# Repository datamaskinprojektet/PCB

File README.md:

## Useful links:
[Kicad Library mangement](https://hackaday.com/2017/05/18/kicad-best-practises-library-management/)
[Kicad git integration](https://jnavila.github.io/plotkicadsch/)

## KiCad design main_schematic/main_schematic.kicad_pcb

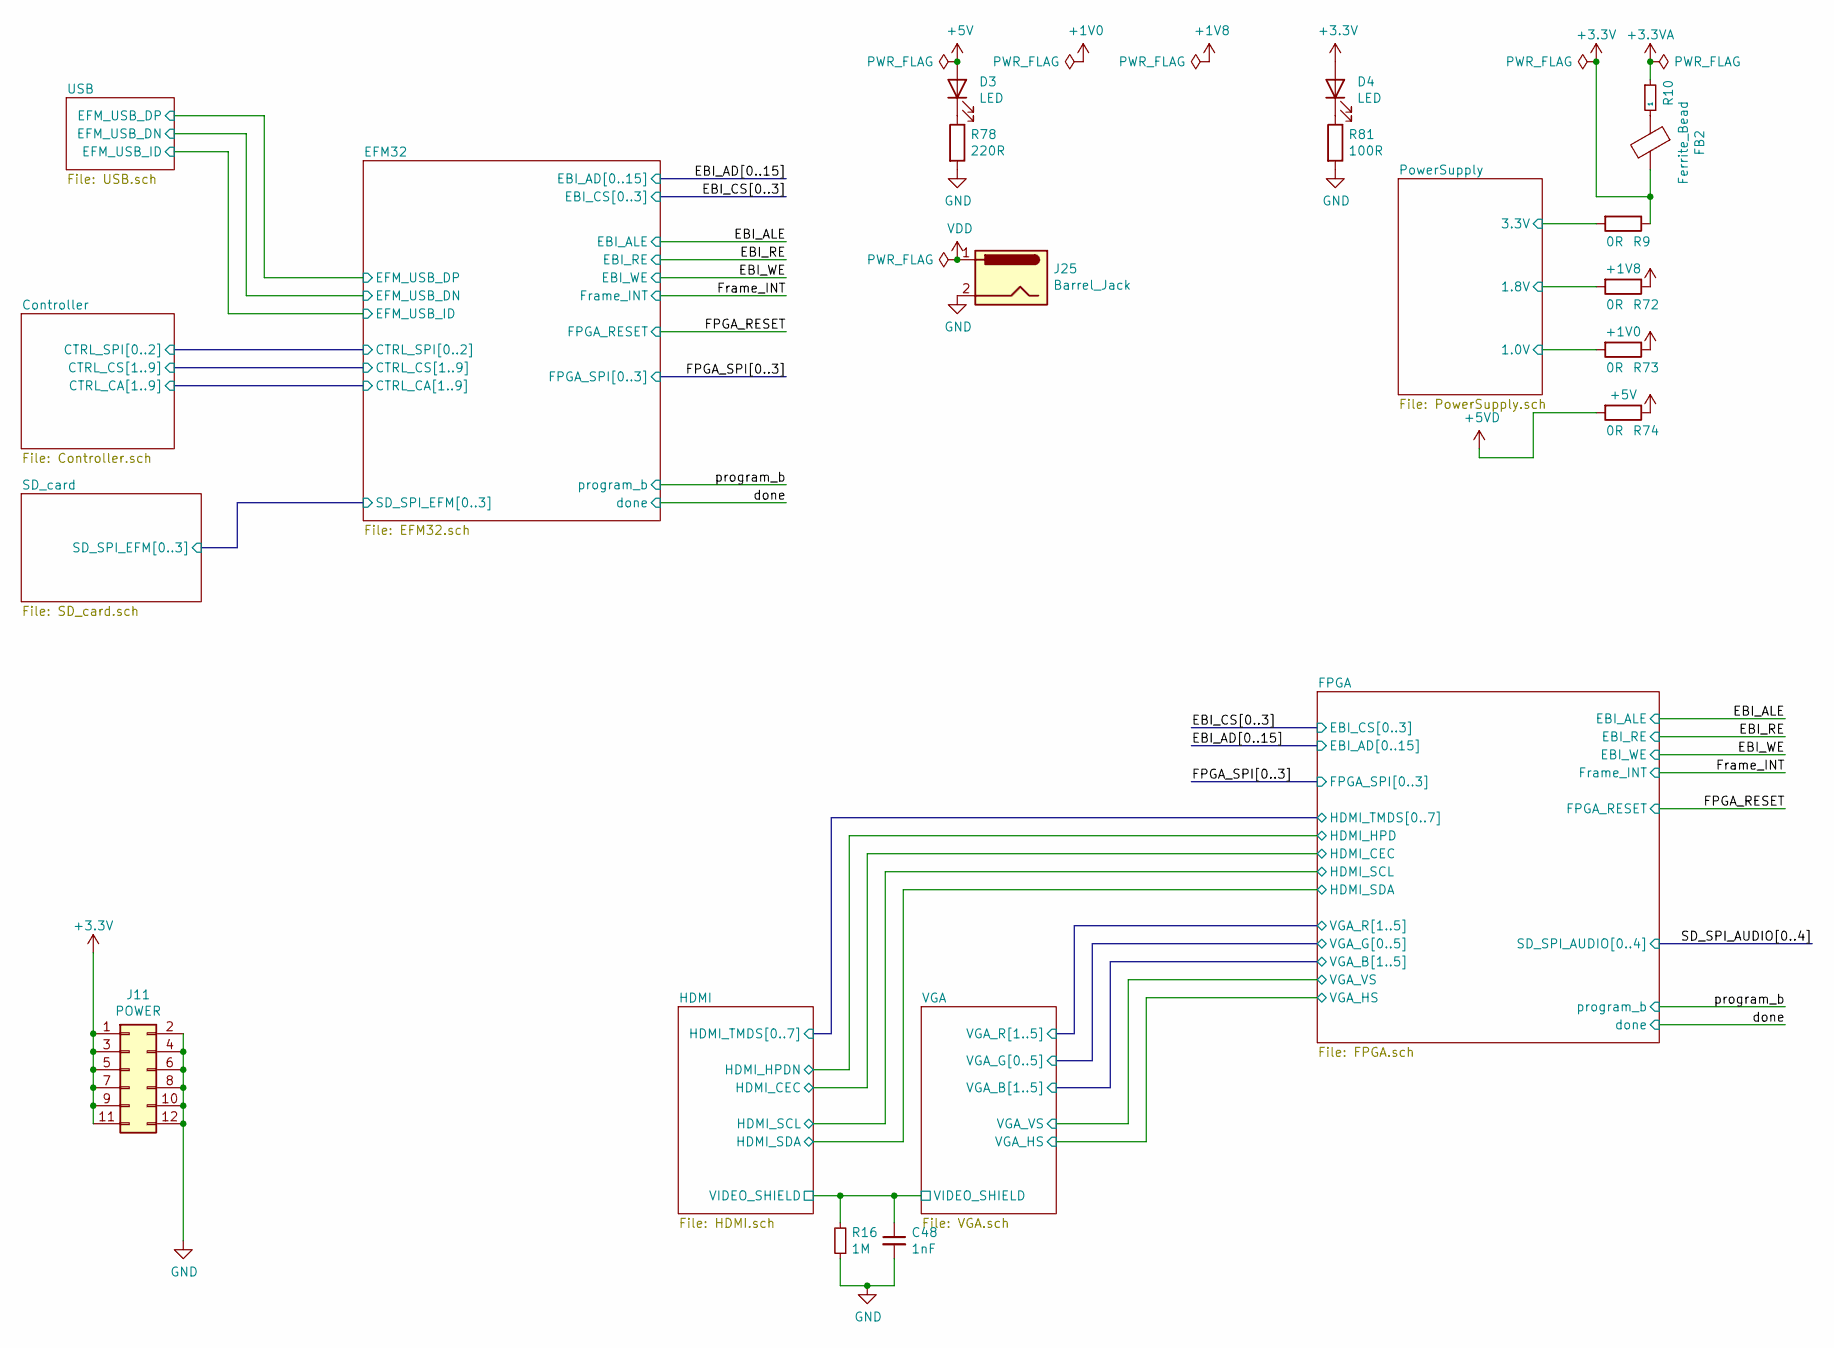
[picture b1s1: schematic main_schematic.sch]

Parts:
C48: 1nF; C_0805_2012Metric
D3, D4: LED; LED_0805_2012Metric
FB2: Ferrite_Bead; R_0805_2012Metric
J11: POWER; PinSocket_2x06_P2.54mm_Vertical_SMD
J25: Barrel_Jack; BarrelJack_Wuerth_6941xx301002
R9, R72, R73, R74: 0R; R_0805_2012Metric
R10: 1; R_0805_2012Metric
R16: 1M; R_0805_2012Metric
R78: 220R; R_0805_2012Metric
R81: 100R; R_0805_2012Metric

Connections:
+1V0: R73.1; also elsewhere on the board
+1V8: R72.1; also elsewhere on the board
+3.3VA: R10.1; also elsewhere on the board
+5V: D3.2 (A), R74.1; also elsewhere on the board
+5VD: R74.2; also elsewhere on the board
/HDMI/VIDEO_SHIELD: C48.1, R16.2; also elsewhere on the board
/PowerSupply/1.0V: R73.2; also elsewhere on the board
/PowerSupply/1.8V: R72.2; also elsewhere on the board
/PowerSupply/3.3V: R9.2; also elsewhere on the board
GND: C48.2, J11.2, J11.4, J11.6, J11.8, J11.10, J11.12, J25.2, R16.1, R78.2, R81.2; also elsewhere on the board
unnamed: D3.1 (K), R78.1
unnamed: D4.1 (K), R81.1
unnamed: FB2.1, R10.2
VDD: J25.1; also elsewhere on the board

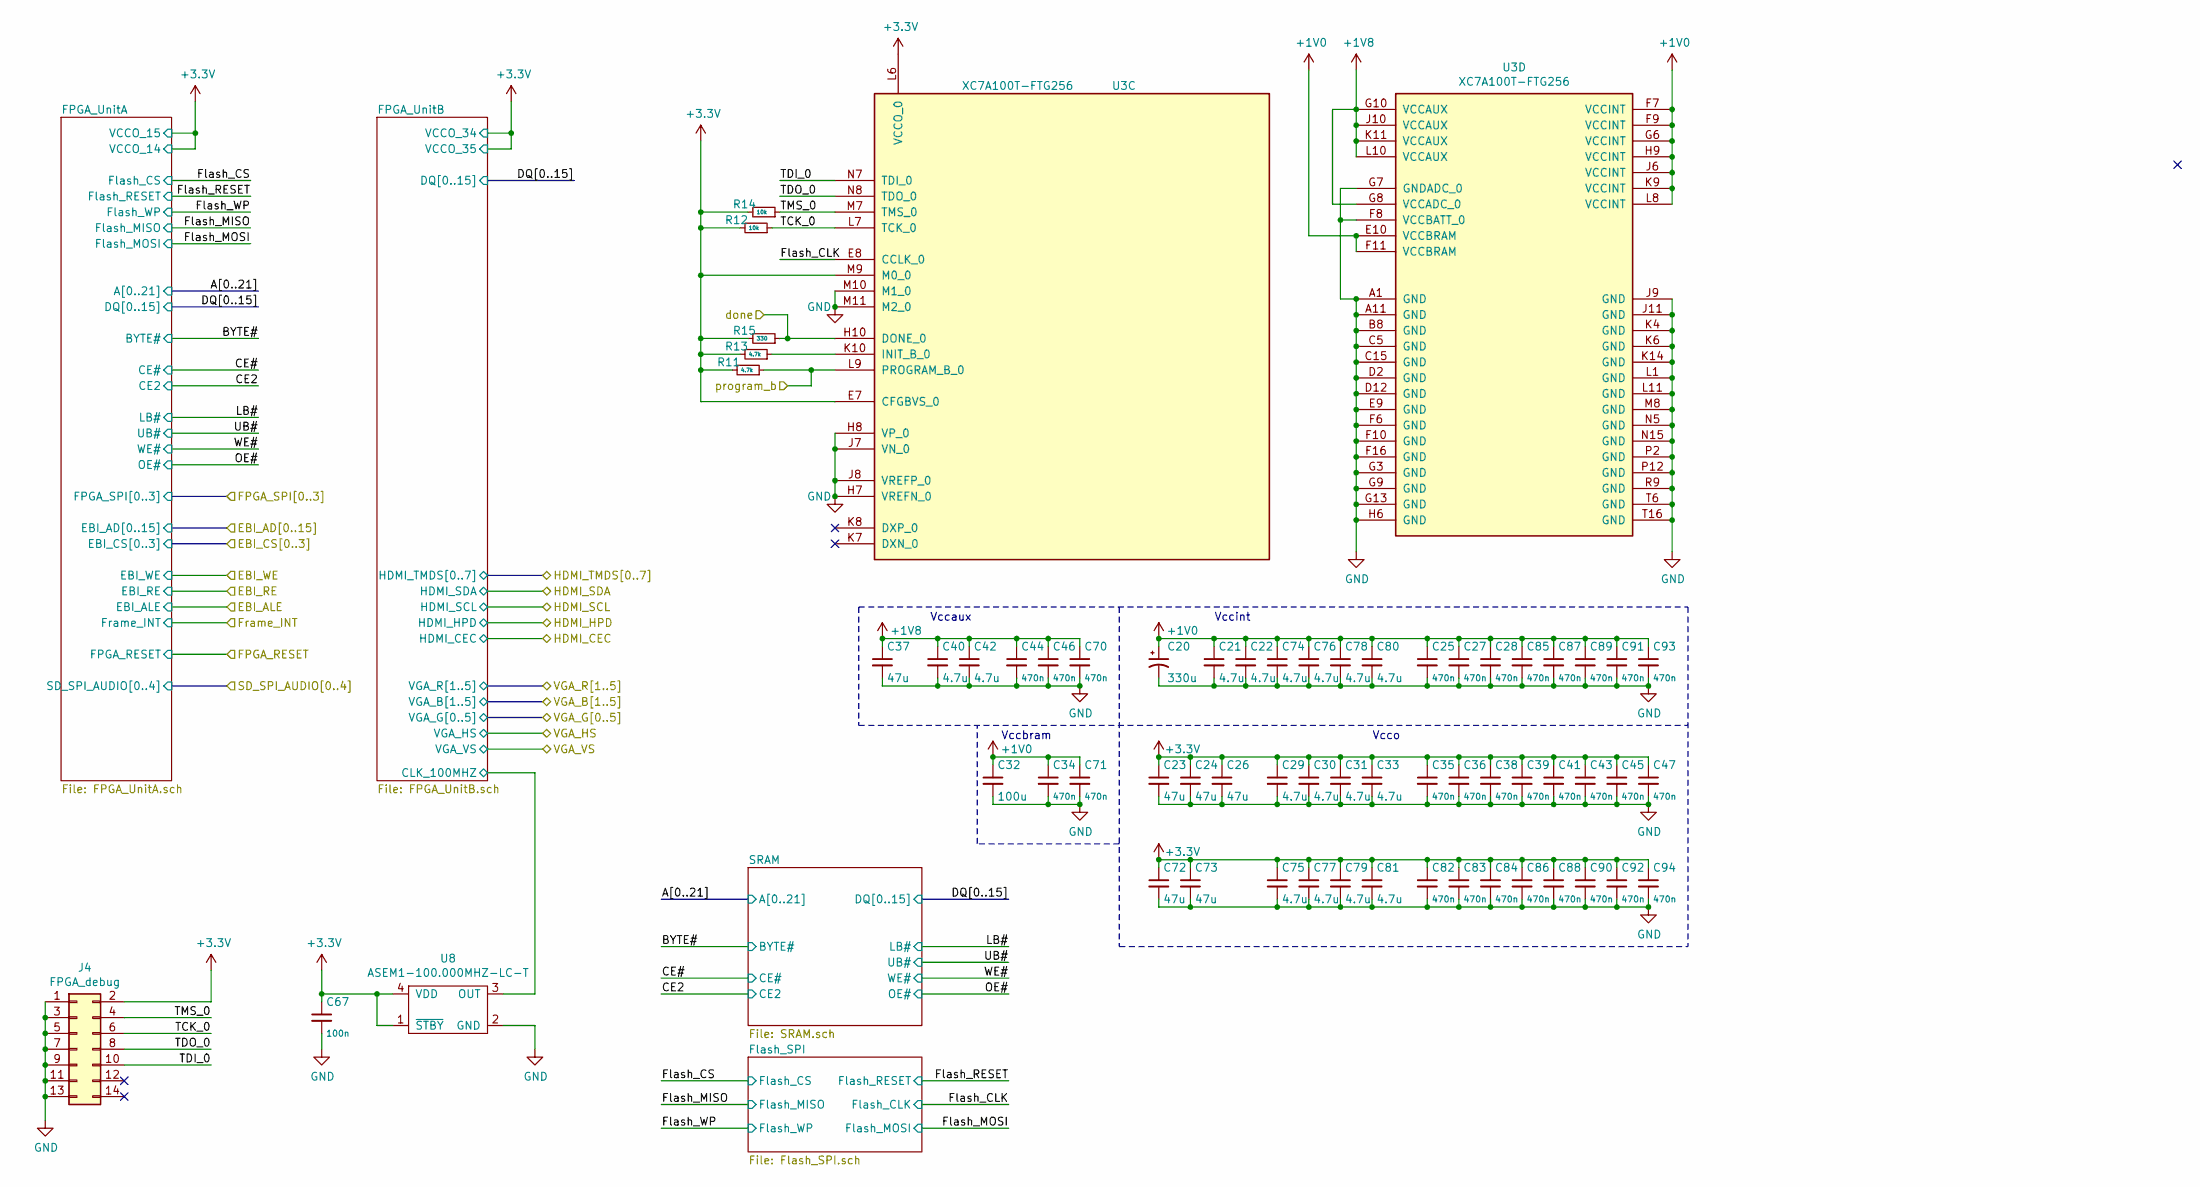
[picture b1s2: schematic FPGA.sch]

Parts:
C20: 330u; CP_EIA-7343-20_Kemet-V
C21, C22, C29, C30, C31, C33, C40, C42, C74, C75, C76, C77, C78, C79, C80, C81: 4.7u; C_0805_2012Metric
C23, C24, C26, C37, C72, C73: 47u; C_1210_3225Metric
C25, C27, C28, C34, C35, C36, C38, C39, C41, C43, C44, C45, C46, C47, C70, C71, C82, C83, C84, C85, C86, C87, C88, C89, C90, C91, C92, C93, C94: 470n; C_0603_1608Metric
C32: 100u; C_1210_3225Metric
C67: 100n; C_0805_2012Metric
J4: FPGA_debug; PinHeader_2x07_P2.00mm_Vertical_SMD
R11, R13: 4.7k; R_0805_2012Metric
R12, R14: 10k; R_0805_2012Metric
R15: 330; R_0805_2012Metric
U3: XC7A100T-FTG256; Xilinx_FTG256
U8: ASEM1-100.000MHZ-LC-T; Oscillator_SMD_Abracon_ASE-4Pin_3.2x2.5mm

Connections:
+1V0: C20.1, C21.1, C22.1, C25.1, C27.1, C28.1, C32.1, C34.1, C71.1, C74.1, C76.1, C78.1, C80.1, C85.1, C87.1, C89.1, C91.1, C93.1, U3.E10 (VCCBRAM), U3.F7 (VCCINT), U3.F9 (VCCINT), U3.F11 (VCCBRAM), U3.G6 (VCCINT), U3.H9 (VCCINT), U3.J6 (VCCINT), U3.K9 (VCCINT), U3.L8 (VCCINT); also elsewhere on the board
+1V8: C37.1, C40.1, C42.1, C44.1, C46.1, C70.1, U3.G8 (VCCADC_0), U3.G10 (VCCAUX), U3.J10 (VCCAUX), U3.K11 (VCCAUX), U3.L10 (VCCAUX); also elsewhere on the board
/FPGA/FPGA_UnitB/CLK_100MHZ: U8.3 (OUT); also elsewhere on the board
/FPGA/Flash_CLK: U3.E8 (CCLK_0); also elsewhere on the board
/FPGA/TCK_0: J4.6, R12.1, U3.L7 (TCK_0)
/FPGA/TDI_0: J4.10, U3.N7 (TDI_0)
/FPGA/TDO_0: J4.8, U3.N8 (TDO_0)
/FPGA/TMS_0: J4.4, R14.1, U3.M7 (TMS_0)
/done: R15.1, U3.H10 (DONE_0); also elsewhere on the board
/program_b: R11.1, U3.L9 (PROGRAM_B_0); also elsewhere on the board
GND: C20.2, C21.2, C22.2, C23.2, C24.2, C25.2, C26.2, C27.2, C28.2, C29.2, C30.2, C31.2, C32.2, C33.2, C34.2, C35.2, C36.2, C37.2, C38.2, C39.2, C40.2, C41.2, C42.2, C43.2, C44.2, C45.2, C46.2, C47.2, C67.2, C70.2, C71.2, C72.2, C73.2, C74.2, C75.2, C76.2, C77.2, C78.2, C79.2, C80.2, C81.2, C82.2, C83.2, C84.2, C85.2, C86.2, C87.2, C88.2, C89.2, C90.2, C91.2, C92.2, C93.2, C94.2, J4.1, J4.3, J4.5, J4.7, J4.9, J4.11, J4.13, U3.A1 (GND), U3.A11 (GND), U3.B8 (GND), U3.C5 (GND), U3.C15 (GND), U3.D2 (GND), U3.D12 (GND), U3.E9 (GND), U3.F6 (GND), U3.F8 (VCCBATT_0), U3.F10 (GND), U3.F16 (GND), U3.G3 (GND), U3.G7 (GNDADC_0), U3.G9 (GND), U3.G13 (GND), U3.H6 (GND), U3.H7 (VREFN_0), U3.H8 (VP_0), U3.J7 (VN_0), U3.J8 (VREFP_0), U3.J9 (GND), U3.J11 (GND), U3.K4 (GND), U3.K6 (GND), U3.K14 (GND), U3.L1 (GND), U3.L11 (GND), U3.M8 (GND), U3.M10 (M1_0), U3.M11 (M2_0), U3.N5 (GND), U3.N15 (GND), U3.P2 (GND), U3.P12 (GND), U3.R9 (GND), U3.T6 (GND), U3.T16 (GND), U8.2 (GND); also elsewhere on the board
unnamed: R13.1, U3.K10 (INIT_B_0)

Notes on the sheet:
Vccaux
Vccbram
Vccint
Vcco

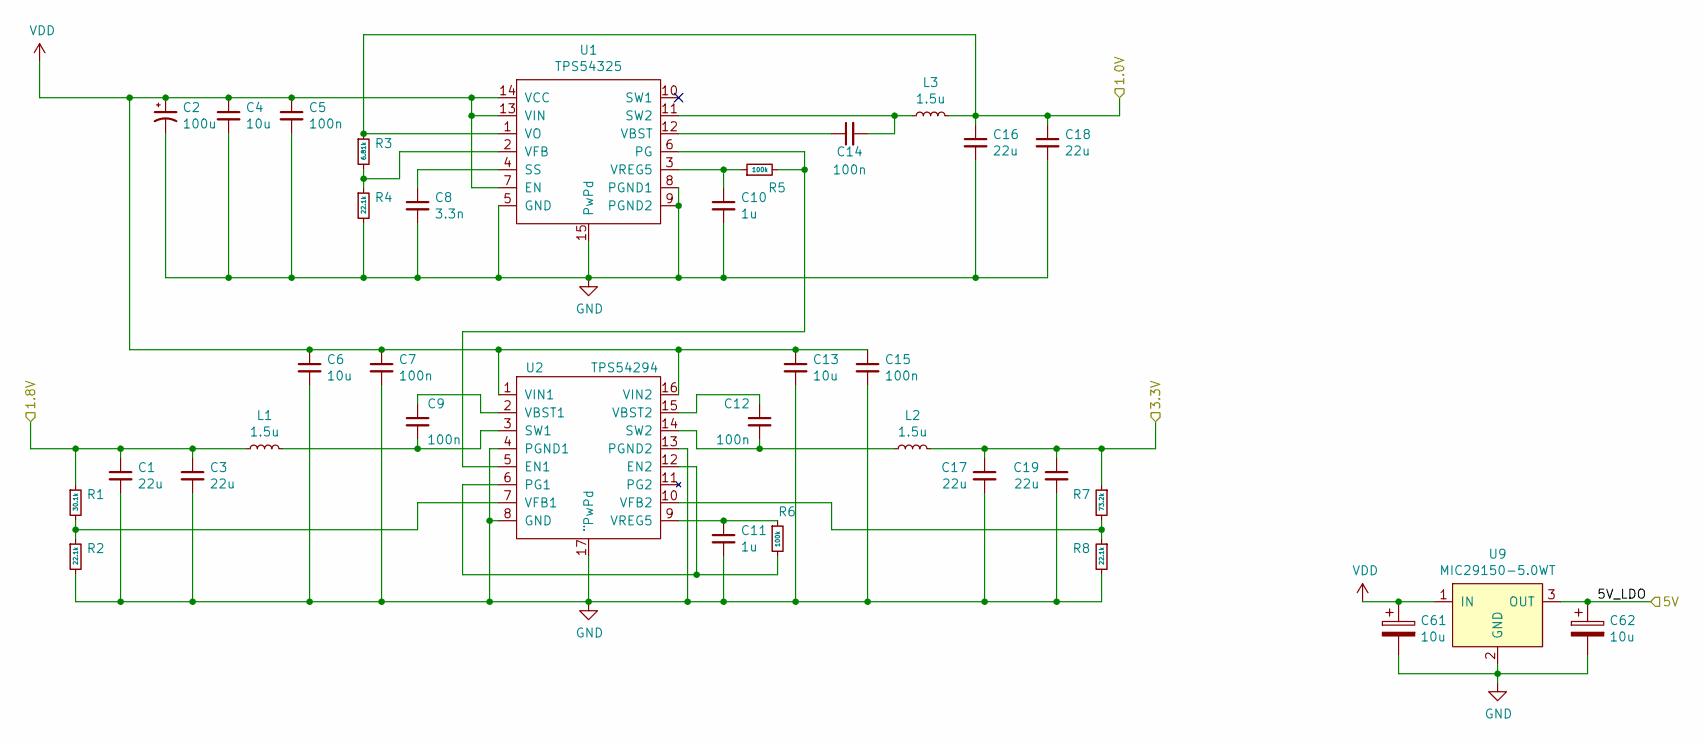
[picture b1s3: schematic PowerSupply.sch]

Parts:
C1, C3, C16, C17, C18, C19: 22u; C_0805_2012Metric
C2: 100u; CP_Elec_6.3x7.7
C4, C6, C13: 10u; C_0805_2012Metric
C5, C7, C9, C12, C14, C15: 100n; C_0805_2012Metric
C8: 3.3n; C_0805_2012Metric
C10, C11: 1u; C_0805_2012Metric
C61, C62: 10u; C_1210_3225Metric
L1, L2, L3: 1.5u; L_Coilcraft_XxL4020
R1: 30.1k; R_0805_2012Metric
R2, R4, R8: 22.1k; R_0805_2012Metric
R3: 6.81k; R_0805_2012Metric
R5, R6: 100k; R_0805_2012Metric
R7: 73.2k; R_0805_2012Metric
U1: TPS54325; HTSSOP-14-1EP_4.4x5mm_P0.65mm_EP3.4x5mm_Mask3x3.1mm
U2: TPS54294; HTSSOP-16-1EP_4.4x5mm_P0.65mm_EP3.4x5mm
U9: MIC29150-5.0WT; TO-220-3_Horizontal_TabUp

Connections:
/PowerSupply/1.0V: C16.1, C18.1, L3.2, R3.1, U1.1 (VO); also elsewhere on the board
/PowerSupply/1.8V: C1.1, C3.1, L1.1, R1.1; also elsewhere on the board
/PowerSupply/3.3V: C17.1, C19.1, L2.1, R7.1; also elsewhere on the board
/PowerSupply/5V: C62.1, U9.3 (OUT)
GND: C1.2, C2.2, C3.2, C4.2, C5.2, C6.2, C7.2, C8.2, C10.2, C11.2, C13.2, C15.2, C16.2, C17.2, C18.2, C19.2, C61.2, C62.2, R2.2, R4.2, R8.2, U1.5 (GND), U1.8 (PGND1), U1.9 (PGND2), U1.15 (PwPd), U2.4 (PGND1), U2.8 (GND), U2.13 (PGND2), U2.17 (¨PwPd), U9.2 (GND); also elsewhere on the board
unnamed: C8.1, U1.4 (SS)
unnamed: C9.1, U2.2 (VBST1)
unnamed: C9.2, L1.2, U2.3 (SW1)
unnamed: C10.1, R5.1, U1.3 (VREG5)
unnamed: C11.1, R6.1, U2.9 (VREG5)
unnamed: C12.1, U2.15 (VBST2)
unnamed: C12.2, L2.2, U2.14 (SW2)
unnamed: C14.1, U1.12 (VBST)
unnamed: C14.2, L3.1, U1.11 (SW2)
unnamed: R1.2, R2.1, U2.7 (VFB1)
unnamed: R3.2, R4.1, U1.2 (VFB)
unnamed: R5.2, U1.6 (PG), U2.5 (EN1)
unnamed: R6.2, U2.6 (PG1), U2.12 (EN2)
unnamed: R7.2, R8.1, U2.10 (VFB2)
VDD: C2.1, C4.1, C5.1, C6.1, C7.1, C13.1, C15.1, C61.1, U1.7 (EN), U1.13 (VIN), U1.14 (VCC), U2.1 (VIN1), U2.16 (VIN2), U9.1 (IN); also elsewhere on the board

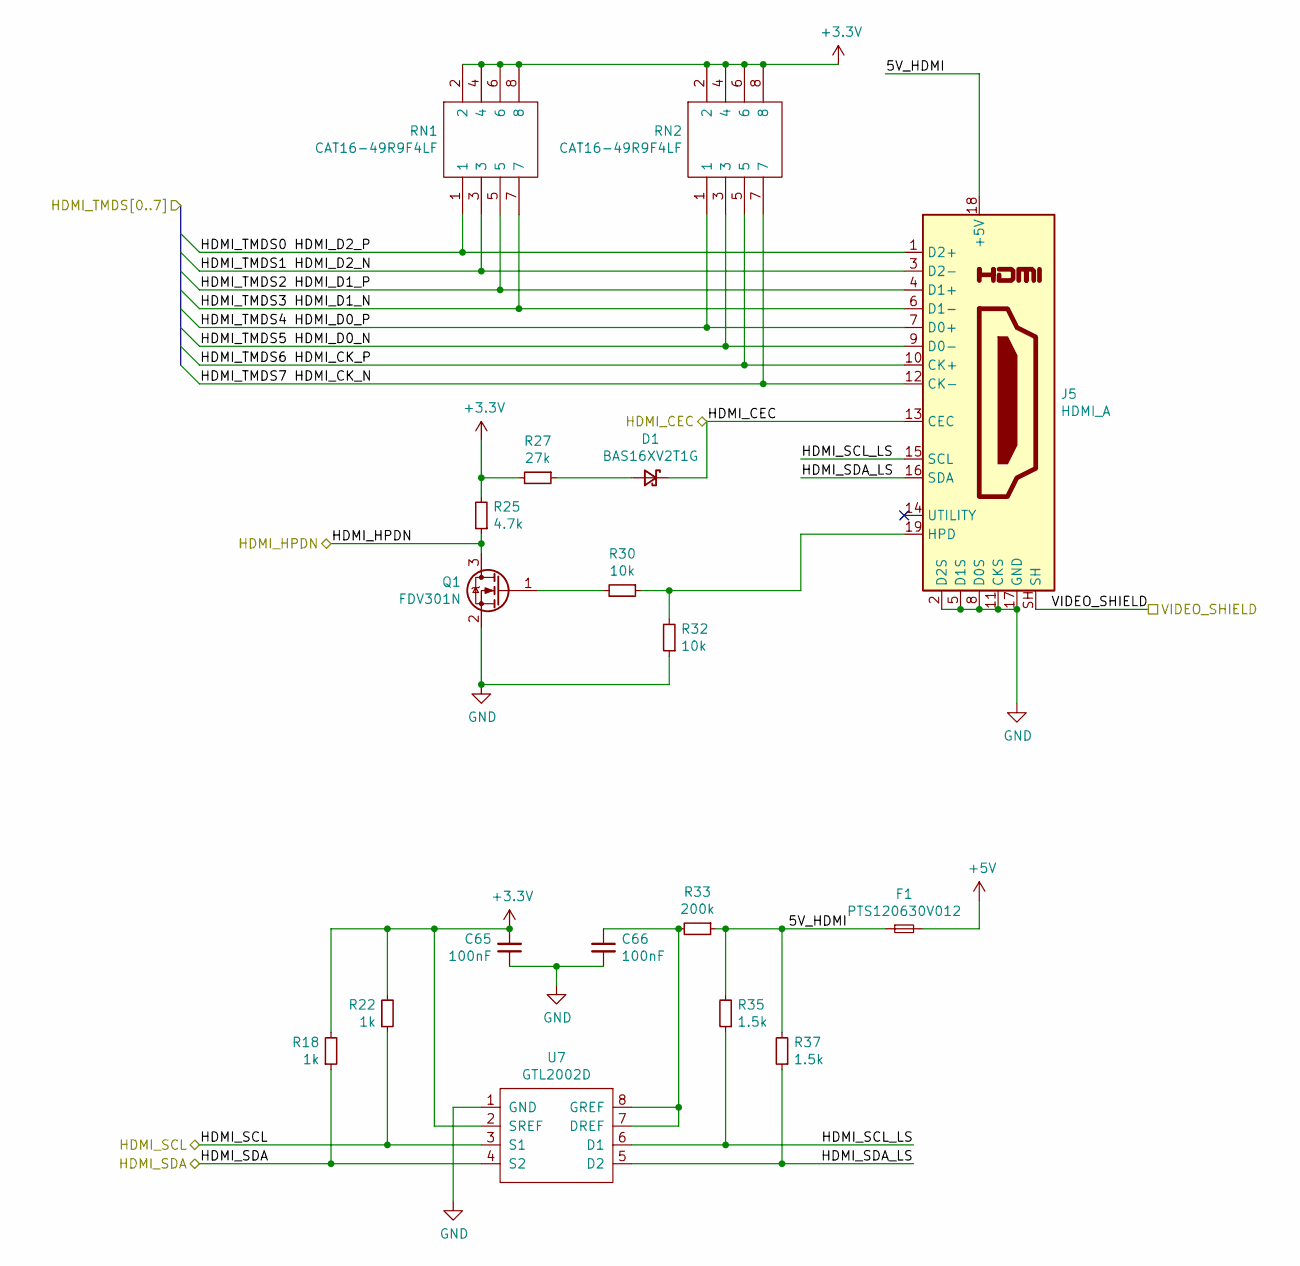
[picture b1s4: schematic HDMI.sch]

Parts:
C65, C66: 100nF; C_0805_2012Metric
D1: BAS16XV2T1G; D_SOD-523
F1: PTS120630V012; Fuse_1206_3216Metric
J5: HDMI_A; HDMI-10029449-111RLF
Q1: FDV301N; SOT-23
R18, R22: 1k; R_0805_2012Metric
R25: 4.7k; R_0805_2012Metric
R27: 27k; R_0805_2012Metric
R30, R32: 10k; R_0805_2012Metric
R33: 200k; R_0805_2012Metric
R35, R37: 1.5k; R_0805_2012Metric
RN1, RN2: CAT16-49R9F4LF; CAT16104J4LF; Mouser Part Number 652-CAT16-49R9F4LF
U7: GTL2002D; SO-8_3.9x4.9mm_P1.27mm

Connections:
+5V: F1.2; also elsewhere on the board
/FPGA/HDMI_CEC: D1.1 (K), J5.13 (CEC); also elsewhere on the board
/FPGA/HDMI_HPD: Q1.3 (D), R25.1; also elsewhere on the board
/FPGA/HDMI_SCL: R22.1, U7.3 (S1); also elsewhere on the board
/FPGA/HDMI_SDA: R18.1, U7.4 (S2); also elsewhere on the board
/HDMI/5V_HDMI: F1.1, J5.18 (+5V), R33.1, R35.2, R37.2
/HDMI/HDMI_CK_N: J5.12 (CK-), RN2.7; also elsewhere on the board
/HDMI/HDMI_CK_P: J5.10 (CK+), RN2.5; also elsewhere on the board
/HDMI/HDMI_D0_N: J5.9 (D0-), RN2.3; also elsewhere on the board
/HDMI/HDMI_D0_P: J5.7 (D0+), RN2.1; also elsewhere on the board
/HDMI/HDMI_D1_N: J5.6 (D1-), RN1.7; also elsewhere on the board
/HDMI/HDMI_D1_P: J5.4 (D1+), RN1.5; also elsewhere on the board
/HDMI/HDMI_D2_N: J5.3 (D2-), RN1.3; also elsewhere on the board
/HDMI/HDMI_D2_P: J5.1 (D2+), RN1.1; also elsewhere on the board
/HDMI/HDMI_SCL_LS: J5.15 (SCL), R35.1, U7.6 (D1)
/HDMI/HDMI_SDA_LS: J5.16 (SDA), R37.1, U7.5 (D2)
/HDMI/VIDEO_SHIELD: J5.SH; also elsewhere on the board
GND: C65.1, C66.2, J5.2 (D2S), J5.5 (D1S), J5.8 (D0S), J5.11 (CKS), J5.17 (GND), Q1.2 (S), R32.1, U7.1 (GND); also elsewhere on the board
unnamed: C66.1, R33.2, U7.7 (DREF), U7.8 (GREF)
unnamed: D1.2 (A), R27.1
unnamed: J5.19 (HPD), R30.1, R32.2
unnamed: Q1.1 (G), R30.2

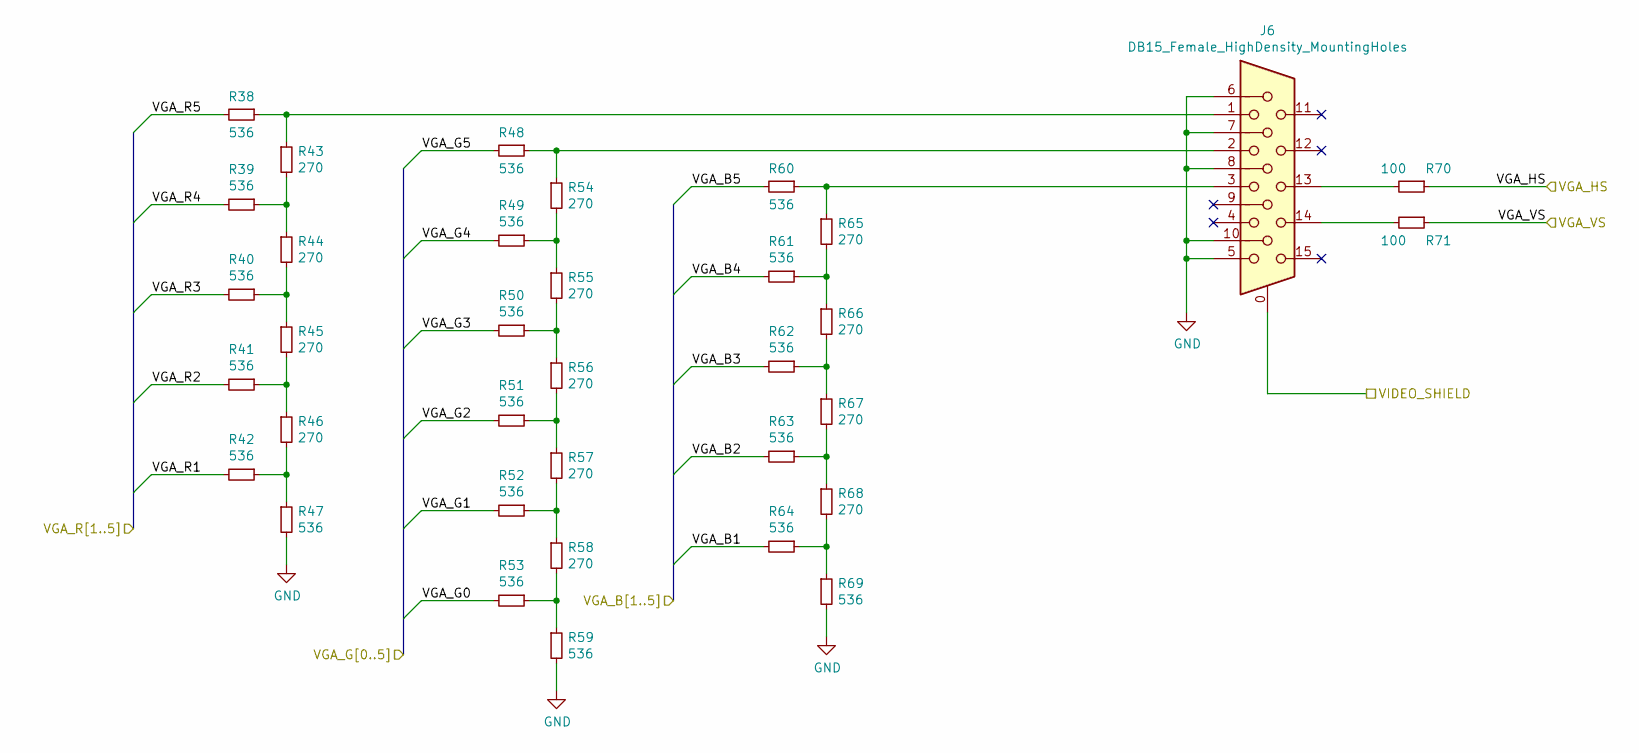
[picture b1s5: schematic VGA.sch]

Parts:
J6: DB15_Female_HighDensity_MountingHoles; DSUB-15-HD_Female_Horizontal_P2.29x1.98mm_EdgePinOffset8.35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
R38, R39, R40, R41, R42, R47, R48, R49, R50, R51, R52, R53, R59, R60, R61, R62, R63, R64, R69: 536; R_0603_1608Metric
R43, R44, R45, R46, R54, R55, R56, R57, R58, R65, R66, R67, R68: 270; R_0603_1608Metric
R70, R71: 100; R_0805_2012Metric

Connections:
/FPGA/VGA_HS: R70.1; also elsewhere on the board
/FPGA/VGA_VS: R71.1; also elsewhere on the board
/HDMI/VIDEO_SHIELD: J6.0; also elsewhere on the board
/VGA/VGA_B1: R64.2; also elsewhere on the board
/VGA/VGA_B2: R63.2; also elsewhere on the board
/VGA/VGA_B3: R62.2; also elsewhere on the board
/VGA/VGA_B4: R61.2; also elsewhere on the board
/VGA/VGA_B5: R60.2; also elsewhere on the board
/VGA/VGA_G0: R53.2; also elsewhere on the board
/VGA/VGA_G1: R52.2; also elsewhere on the board
/VGA/VGA_G2: R51.2; also elsewhere on the board
/VGA/VGA_G3: R50.2; also elsewhere on the board
/VGA/VGA_G4: R49.2; also elsewhere on the board
/VGA/VGA_G5: R48.2; also elsewhere on the board
/VGA/VGA_R1: R42.2; also elsewhere on the board
/VGA/VGA_R2: R41.2; also elsewhere on the board
/VGA/VGA_R3: R40.2; also elsewhere on the board
/VGA/VGA_R4: R39.2; also elsewhere on the board
/VGA/VGA_R5: R38.2; also elsewhere on the board
GND: J6.5, J6.6, J6.7, J6.8, J6.10, R47.2, R59.2, R69.2; also elsewhere on the board
unnamed: J6.1, R38.1, R43.1
unnamed: J6.2, R48.1, R54.1
unnamed: J6.3, R60.1, R65.1
unnamed: J6.13, R70.2
unnamed: J6.14, R71.2
unnamed: R39.1, R43.2, R44.1
unnamed: R40.1, R44.2, R45.1
unnamed: R41.1, R45.2, R46.1
unnamed: R42.1, R46.2, R47.1
unnamed: R49.1, R54.2, R55.1
unnamed: R50.1, R55.2, R56.1
unnamed: R51.1, R56.2, R57.1
unnamed: R52.1, R57.2, R58.1
unnamed: R53.1, R58.2, R59.1
unnamed: R61.1, R65.2, R66.1
unnamed: R62.1, R66.2, R67.1
unnamed: R63.1, R67.2, R68.1
unnamed: R64.1, R68.2, R69.1

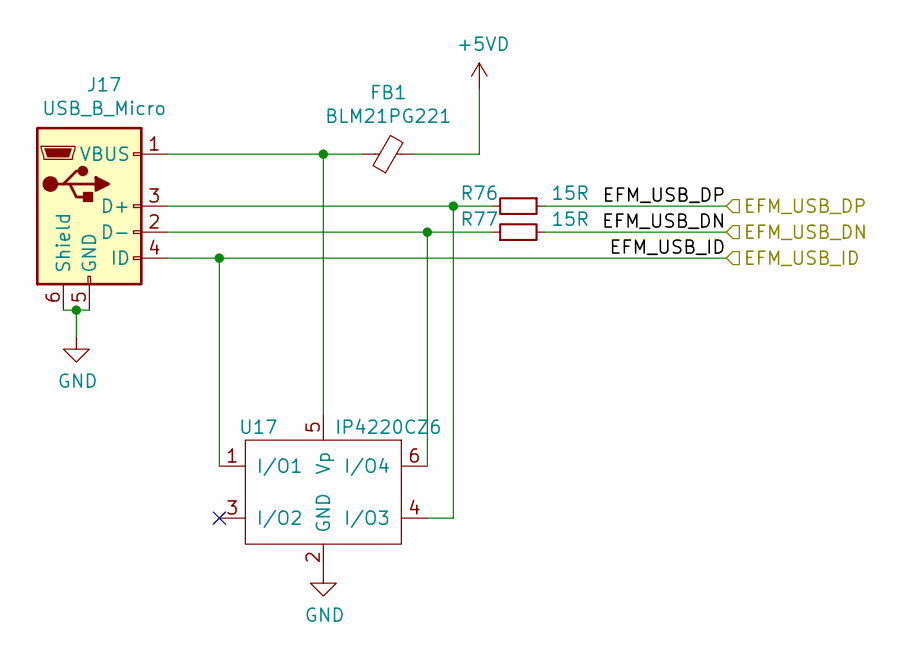
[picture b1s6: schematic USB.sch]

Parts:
FB1: BLM21PG221; L_0805_2012Metric
J17: USB_B_Micro; USB_Micro-B_Molex-105017-0001
R76, R77: 15R; R_0805_2012Metric
U17: IP4220CZ6; TSOP-6_1.65x3.05mm_P0.95mm

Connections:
+5VD: FB1.2; also elsewhere on the board
/EFM32/EFM_USB_DN: R77.2; also elsewhere on the board
/EFM32/EFM_USB_DP: R76.1; also elsewhere on the board
/EFM32/EFM_USB_ID: J17.4 (ID), U17.1 (I/O1); also elsewhere on the board
GND: J17.5 (GND), J17.6 (Shield), U17.2 (GND); also elsewhere on the board
unnamed: FB1.1, J17.1 (VBUS), U17.5 (Vp)
unnamed: J17.2 (D-), R77.1, U17.6 (I/O4)
unnamed: J17.3 (D+), R76.2, U17.4 (I/O3)
